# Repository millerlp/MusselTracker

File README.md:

This repository contains hardware designs and software to create a low-cost datalogger that can be used to track mussel (bivalve molluscs, not muscles) behavior  and temperature over long periods of time. The basic design includes a thermocouple temperature sensor, a hall effect magnetic sensor to sense valve gape, and a 3-D acclerometer/magnetometer to record mussel shell orientation.

Arduino-style code to run the datalogger is available the MusselTracker2 directory. The code requires the use of the MusselTrackerlib library available separately at https://github.com/millerlp/MusselTrackerlib 

Various testing code for individual sensors and the overall circuit board are available in the test_sketches directory. 

Circuit board designs are available in the Eagle_files directory.

Orginally a fork of https://github.com/andrewpetersen/MusselTracker/, now with a wholesale rewrite of the software and hardware. 

******************
    Copyright Luke Miller 2015

    This program is free software: you can redistribute it and/or modify
    it under the terms of the GNU General Public License as published by
    the Free Software Foundation, either version 3 of the License, or
    (at your option) any later version.

    This program is distributed in the hope that it will be useful,
    but WITHOUT ANY WARRANTY; without even the implied warranty of
    MERCHANTABILITY or FITNESS FOR A PARTICULAR PURPOSE.  See the
    GNU General Public License for more details.

    You should have received a copy of the GNU General Public License
    along with this program.  If not, see <http://www.gnu.org/licenses/>.

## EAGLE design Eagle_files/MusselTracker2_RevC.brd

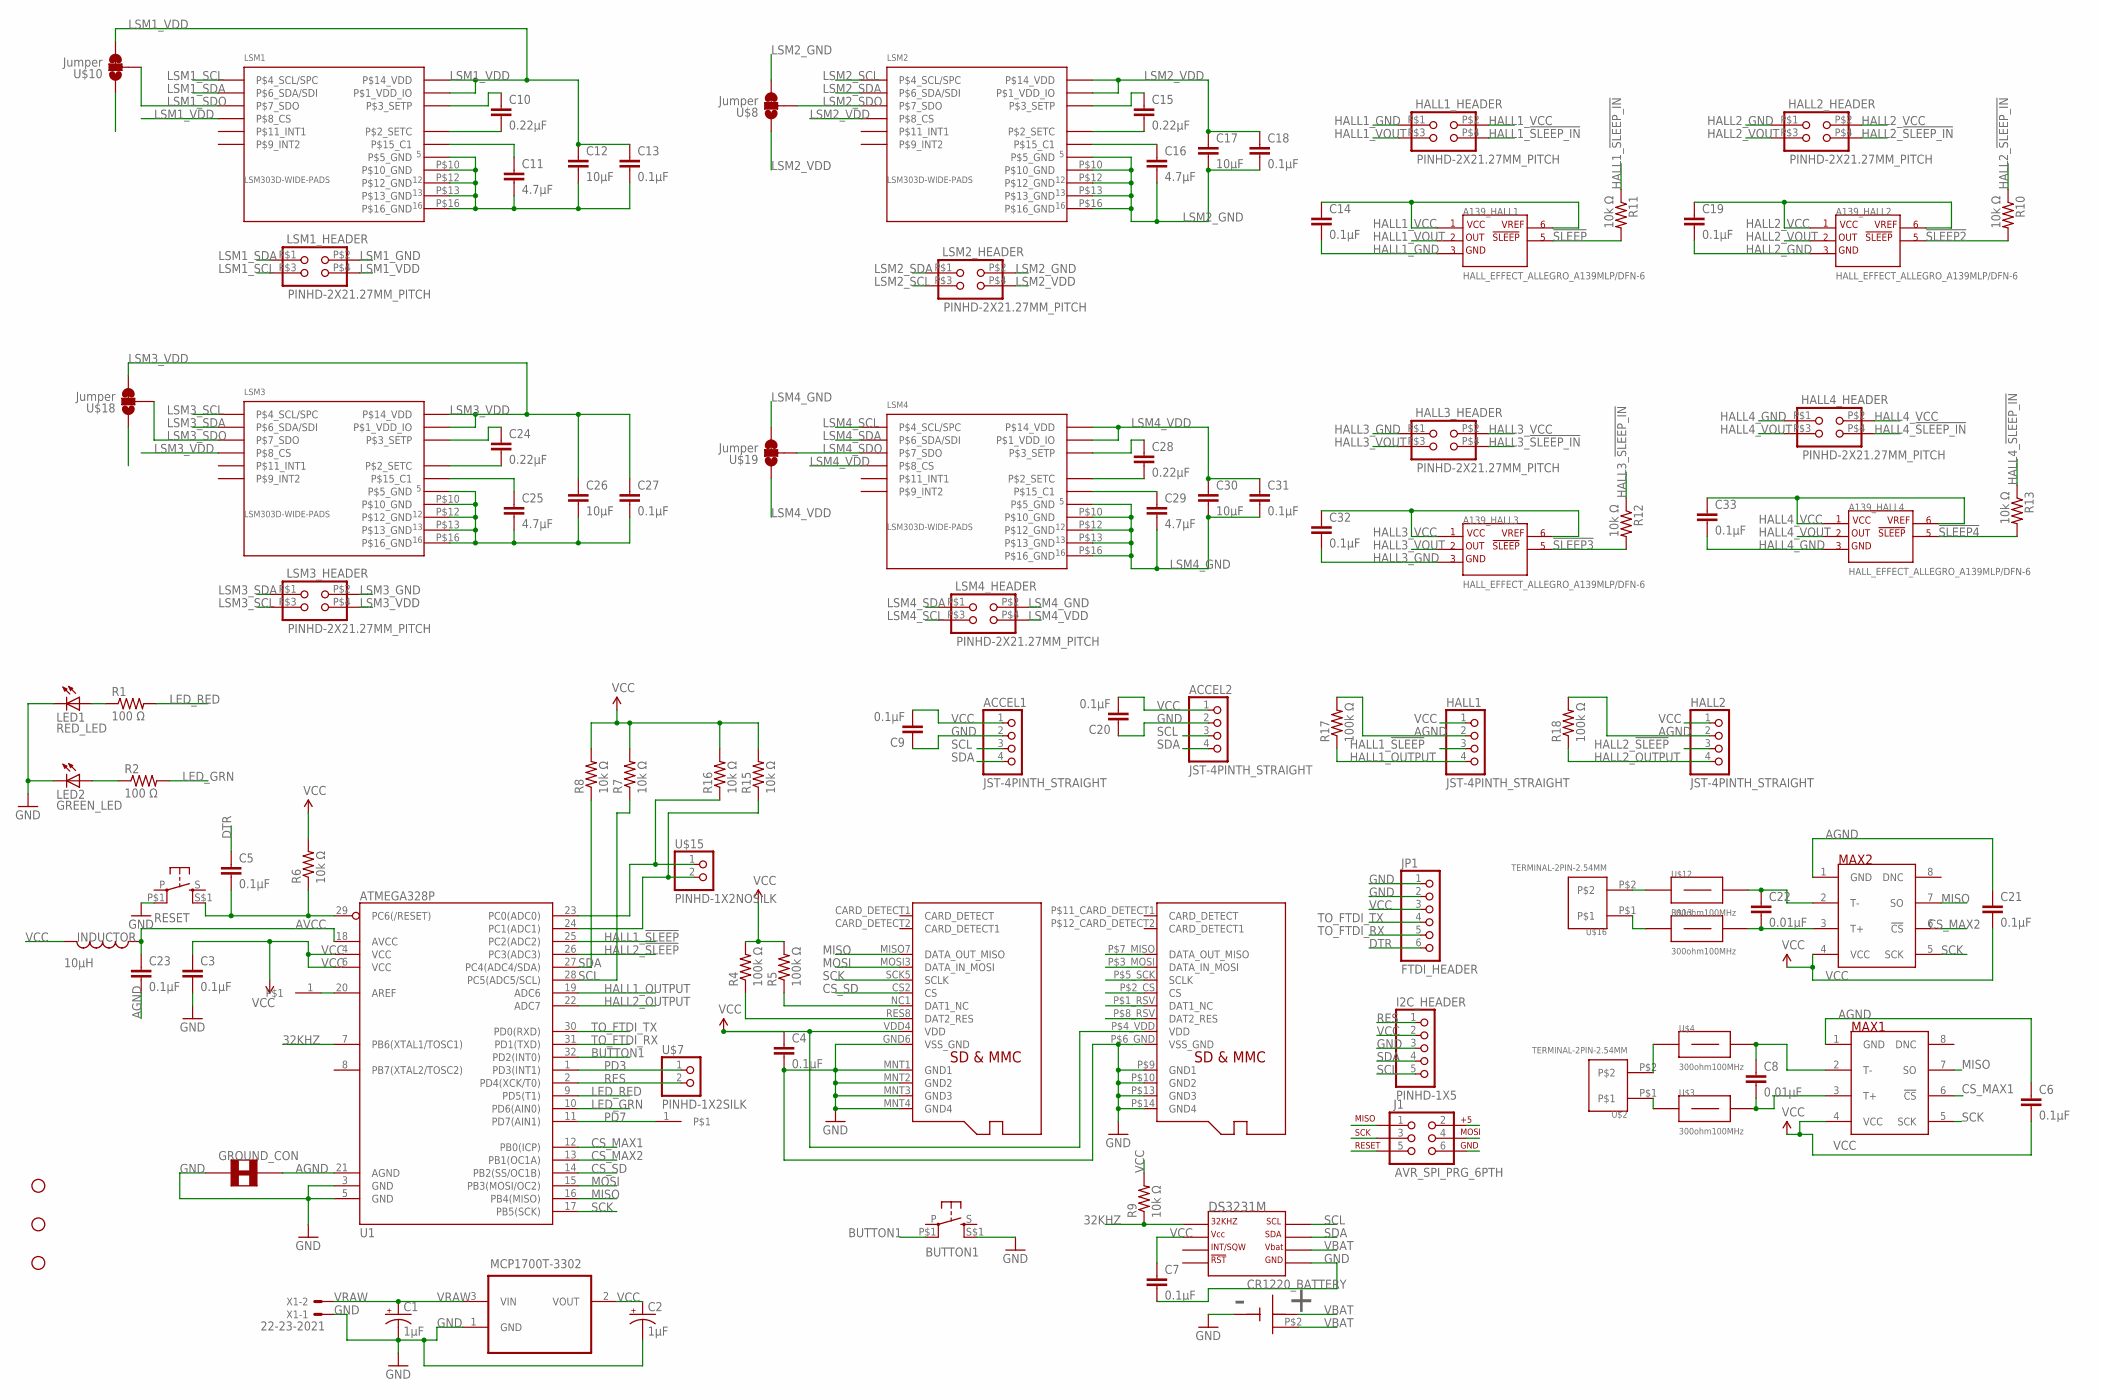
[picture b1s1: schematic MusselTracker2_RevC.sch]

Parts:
A139_HALL1, A139_HALL2, A139_HALL3, A139_HALL4: HALL_EFFECT_ALLEGRO_A139MLP/DFN-6; A139*_HALL_EFFECT
ACCEL1, ACCEL2: JST-4PINTH_STRAIGHT; JST-PH-4-THM
BUTTON1: PUSHBUTTON_DPST_SMD
C1, C2: 1µF; PANASONIC_B
C3, C4, C5, C6, C7, C9, C13, C14, C18, C19, C20, C21, C23, C27, C31, C32, C33: 0.1µF; 0805
C8, C22: 0.01µF; 0805_CAP_50V_KEMET
C10, C15, C24, C28: 0.22µF; 0805
C11, C16, C25, C29: 4.7µF; 0805
C12, C17, C26, C30: 10µF; 0805
CR1220_BATTERY: CR1220_BATTERY_HOLDERSMD; CR1220_BATTERY_HOLDER_SMD
DS3231M: DS3231MSOIC-8; DS3231M_SOIC8
GROUND_CON: SOLDER_JUMPER_TRACESTANDARD; SJ_2S-TRACE
HALL1, HALL2: JST-4PINTH_STRAIGHT; JST-PH-4-THM
HALL1_HEADER, HALL2_HEADER, HALL3_HEADER, HALL4_HEADER: PINHD-2X21.27MM_PITCH; 2X2_1.27MM
I2C_HEADER: PINHD-1X5; 1X05_BIGLOCK
INDUCTOR: 10µH; I_0805
J1: AVR_SPI_PRG_6PTH; 2X3
JP1: FTDI_HEADER; 1X06-BIGLOCK
LED1: RED_LED; CHIPLED_0805
LED2: GREEN_LED; CHIPLED_0805
LSM1, LSM2, LSM3, LSM4: LSM303D-WIDE-PADS; LSM303D
LSM1_HEADER, LSM2_HEADER, LSM3_HEADER, LSM4_HEADER: PINHD-2X21.27MM_PITCH; 2X2_1.27MM
MAX1, MAX2: MAX31855; SO08
MCP1700T-3302: MCP1700T-3302E/TT; SOT95P237X112-3N
R1, R2: 100 Ω; R0805
R4, R5, R17, R18: 100k Ω; R0805
R6, R7, R8, R9, R10, R11, R12, R13, R15, R16: 10k Ω; R0805
RESET: PUSHBUTTON_DPST_SMD
STANDOFF1, STANDOFF2, STANDOFF3: STAND-OFF
U1: ATMEGA328P; TQFP32-08
U$1: MICROSD_MOLEX_REVERSECURRENT; MICROSD_SOCKET_MOLEX_REVERSEMOUNT
U$2, U$16: TERMINAL-2PIN-2.54MM
U$3, U$4, U$12, U$13: 300ohm100MHz; 0805
U$6, U$17: PINHD-1X1SMALL; 1X01_SMALL
U$7: PINHD-1X2SILK; 1X02
U$8, U$10, U$18, U$19: Jumper; PAD-JUMPER-3-2OF3_NC_BY_TRACE_SMALL
U$14: MICROSD_MOLEX_REVERSEOBSOLETE; MICROSD_SOCKET_MOLEX_REVERSEMOUNT_OBSOLETE
U$15: PINHD-1X2NOSILK; 1X02_NOSILK
X1: 22-23-2021

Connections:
32KHZ: DS3231M.1 (P$1_32KHZ), R9.1, U1.7 (PB6(XTAL1/TOSC1))
!SLEEP: A139_HALL1.P$5, R11.2
!SLEEP2: A139_HALL2.P$5, R10.2
!SLEEP3: A139_HALL3.P$5, R12.2
!SLEEP4: A139_HALL4.P$5, R13.2
AGND: C6.1, C21.1, C23.2, GROUND_CON.2, HALL1.2, HALL2.2, MAX1.1 (GND), MAX2.1 (GND), R17.2, R18.2, U1.21 (AGND)
AVCC: C23.1, INDUCTOR.P$1 (1), U1.18 (AVCC)
BUTTON1: BUTTON1.P$1 (P1), U1.32 (PD2(INT0))
CS_MAX1: MAX1.6 (!CS), U1.12 (PB0(ICP))
CS_MAX2: MAX2.6 (!CS), U1.13 (PB1(OC1A))
CS_SD: U1.14 (PB2(SS/OC1B)), U$1.CS2 (CS), U$14.P$2_CS (CS)
DTR: C5.1, JP1.6
GND: ACCEL1.2, ACCEL2.2, BUTTON1.S$1 (S1), C1.-, C2.-, C3.2, C4.2, C7.2, C9.1, C20.1, CR1220_BATTERY.GND, DS3231M.5 (P$5_GND), GROUND_CON.1, I2C_HEADER.3, J1.6, JP1.1, JP1.2, LED1.C, LED2.C, MCP1700T-3302.1 (GND), RESET.P$1 (P1), U1.3 (GND), U1.5 (GND), U$1.GND6 (VSS_GND), U$1.MNT1 (GND1), U$1.MNT2 (GND2), U$1.MNT3 (GND3), U$1.MNT4 (GND4), U$14.P$6_GND (VSS_GND), U$14.P$9 (GND1), U$14.P$10 (GND2), U$14.P$13 (GND3), U$14.P$14 (GND4), X1.1
HALL1_!SLEEP: HALL1.3, U1.25 (PC2(ADC2))
HALL1_!SLEEP_IN: HALL1_HEADER.P$4 (4), R11.1
HALL1_GND: A139_HALL1.P$3_4, C14.2, HALL1_HEADER.P$1 (1)
HALL1_OUTPUT: HALL1.4, R17.1, U1.19 (ADC6)
HALL1_VCC: A139_HALL1.P$1, A139_HALL1.P$6, C14.1, HALL1_HEADER.P$2 (2)
HALL1_VOUT: A139_HALL1.P$2, HALL1_HEADER.P$3 (3)
HALL2_!SLEEP: HALL2.3, U1.26 (PC3(ADC3))
HALL2_!SLEEP_IN: HALL2_HEADER.P$4 (4), R10.1
HALL2_GND: A139_HALL2.P$3_4, C19.2, HALL2_HEADER.P$1 (1)
HALL2_OUTPUT: HALL2.4, R18.1, U1.22 (ADC7)
HALL2_VCC: A139_HALL2.P$1, A139_HALL2.P$6, C19.1, HALL2_HEADER.P$2 (2)
HALL2_VOUT: A139_HALL2.P$2, HALL2_HEADER.P$3 (3)
HALL3_!SLEEP_IN: HALL3_HEADER.P$4 (4), R12.1
HALL3_GND: A139_HALL3.P$3_4, C32.2, HALL3_HEADER.P$1 (1)
HALL3_VCC: A139_HALL3.P$1, A139_HALL3.P$6, C32.1, HALL3_HEADER.P$2 (2)
HALL3_VOUT: A139_HALL3.P$2, HALL3_HEADER.P$3 (3)
HALL4_!SLEEP_IN: HALL4_HEADER.P$4 (4), R13.1
HALL4_GND: A139_HALL4.P$3_4, C33.2, HALL4_HEADER.P$1 (1)
HALL4_VCC: A139_HALL4.P$1, A139_HALL4.P$6, C33.1, HALL4_HEADER.P$2 (2)
HALL4_VOUT: A139_HALL4.P$2, HALL4_HEADER.P$3 (3)
LED_GRN: R2.2, U1.10 (PD6(AIN0))
LED_RED: R1.2, U1.9 (PD5(T1))
LSM1_GND: C11.2, C12.2, C13.2, LSM1.P$5 (P$5_GND), LSM1.P$10 (P$10_GND), LSM1.P$12 (P$12_GND), LSM1.P$13 (P$13_GND), LSM1.P$16 (P$16_GND), LSM1_HEADER.P$2 (2), U$10.1
LSM1_SCL: LSM1.P$4 (P$4_SCL/SPC), LSM1_HEADER.P$3 (3)
LSM1_SDA: LSM1.P$6 (P$6_SDA/SDI), LSM1_HEADER.P$1 (1)
LSM1_SDO: LSM1.P$7 (P$7_SDO), U$10.2
LSM1_VDD: C12.1, C13.1, LSM1.P$1 (P$1_VDD_IO), LSM1.P$8 (P$8_CS), LSM1.P$14 (P$14_VDD), LSM1_HEADER.P$4 (4), U$10.3
LSM2_GND: C16.2, C17.2, C18.2, LSM2.P$5 (P$5_GND), LSM2.P$10 (P$10_GND), LSM2.P$12 (P$12_GND), LSM2.P$13 (P$13_GND), LSM2.P$16 (P$16_GND), LSM2_HEADER.P$2 (2), U$8.3
LSM2_SCL: LSM2.P$4 (P$4_SCL/SPC), LSM2_HEADER.P$3 (3)
LSM2_SDA: LSM2.P$6 (P$6_SDA/SDI), LSM2_HEADER.P$1 (1)
LSM2_SDO: LSM2.P$7 (P$7_SDO), U$8.2
LSM2_VDD: C17.1, C18.1, LSM2.P$1 (P$1_VDD_IO), LSM2.P$8 (P$8_CS), LSM2.P$14 (P$14_VDD), LSM2_HEADER.P$4 (4), U$8.1
LSM3_GND: C25.2, C26.2, C27.2, LSM3.P$5 (P$5_GND), LSM3.P$10 (P$10_GND), LSM3.P$12 (P$12_GND), LSM3.P$13 (P$13_GND), LSM3.P$16 (P$16_GND), LSM3_HEADER.P$2 (2), U$18.1
LSM3_SCL: LSM3.P$4 (P$4_SCL/SPC), LSM3_HEADER.P$3 (3)
LSM3_SDA: LSM3.P$6 (P$6_SDA/SDI), LSM3_HEADER.P$1 (1)
LSM3_SDO: LSM3.P$7 (P$7_SDO), U$18.2
LSM3_VDD: C26.1, C27.1, LSM3.P$1 (P$1_VDD_IO), LSM3.P$8 (P$8_CS), LSM3.P$14 (P$14_VDD), LSM3_HEADER.P$4 (4), U$18.3
LSM4_GND: C29.2, C30.2, C31.2, LSM4.P$5 (P$5_GND), LSM4.P$10 (P$10_GND), LSM4.P$12 (P$12_GND), LSM4.P$13 (P$13_GND), LSM4.P$16 (P$16_GND), LSM4_HEADER.P$2 (2), U$19.3
LSM4_SCL: LSM4.P$4 (P$4_SCL/SPC), LSM4_HEADER.P$3 (3)
LSM4_SDA: LSM4.P$6 (P$6_SDA/SDI), LSM4_HEADER.P$1 (1)
LSM4_SDO: LSM4.P$7 (P$7_SDO), U$19.2
LSM4_VDD: C30.1, C31.1, LSM4.P$1 (P$1_VDD_IO), LSM4.P$8 (P$8_CS), LSM4.P$14 (P$14_VDD), LSM4_HEADER.P$4 (4), U$19.1
MISO: J1.1, MAX1.7 (SO), MAX2.7 (SO), U1.16 (PB4(MISO)), U$1.MISO7 (DATA_OUT_MISO), U$14.P$7_MISO (DATA_OUT_MISO)
MOSI: J1.4, U1.15 (PB3(MOSI/OC2)), U$1.MOSI3 (DATA_IN_MOSI), U$14.P$3_MOSI (DATA_IN_MOSI)
unnamed: U$2.P$2, U$4.1
unnamed: LED1.A, R1.1
unnamed: U$2.P$1, U$3.1
unnamed: C11.1, LSM1.P$15 (P$15_C1)
unnamed: C10.2, LSM1.P$2 (P$2_SETC)
unnamed: R16.1, U1.23 (PC0(ADC0)), U$15.1
unnamed: U1.20 (AREF), U$17.1
unnamed: R15.1, U1.24 (PC1(ADC1)), U$15.2
unnamed: LED2.A, R2.1
unnamed: U$12.1, U$16.P$2
unnamed: U$13.1, U$16.P$1
unnamed: C24.2, LSM3.P$2 (P$2_SETC)
unnamed: C24.1, LSM3.P$3 (P$3_SETP)
unnamed: C10.1, LSM1.P$3 (P$3_SETP)
unnamed: C15.2, LSM2.P$2 (P$2_SETC)
unnamed: C15.1, LSM2.P$3 (P$3_SETP)
unnamed: C16.1, LSM2.P$15 (P$15_C1)
unnamed: C25.1, LSM3.P$15 (P$15_C1)
unnamed: C28.1, LSM4.P$3 (P$3_SETP)
unnamed: C28.2, LSM4.P$2 (P$2_SETC)
unnamed: C29.1, LSM4.P$15 (P$15_C1)
NC1: R5.1, U$1.NC1 (DAT1_NC), U$14.P$1_RSV (DAT1_NC)
PD3: U1.1 (PD3(INT1)), U$7.1
PD7: U1.11 (PD7(AIN1)), U$6.1
RES: I2C_HEADER.1, U1.2 (PD4(XCK/T0)), U$7.2
RES8: R4.1, U$1.RES8 (DAT2_RES), U$14.P$8_RSV (DAT2_RES)
RESET: C5.2, J1.5, R6.1, RESET.S$1 (S1), U1.29 (PC6(/RESET))
SCK: J1.3, MAX1.5 (SCK), MAX2.5 (SCK), U1.17 (PB5(SCK)), U$1.SCK5 (SCLK), U$14.P$5_SCK (SCLK)
SCL: ACCEL1.3, ACCEL2.3, DS3231M.8 (P$8_SCL), I2C_HEADER.5, R7.1, U1.28 (PC5(ADC5/SCL))
SDA: ACCEL1.4, ACCEL2.4, DS3231M.7 (P$7_SDA), I2C_HEADER.4, R8.1, U1.27 (PC4(ADC4/SDA))
T+_MAX1: C8.2, MAX1.3 (T+), U$3.2
T+_MAX2: C22.2, MAX2.3 (T+), U$13.2
T-_MAX1: C8.1, MAX1.2 (T-), U$4.2
T-_MAX2: C22.1, MAX2.2 (T-), U$12.2
TO_FTDI_RX: JP1.5, U1.31 (PD1(TXD))
TO_FTDI_TX: JP1.4, U1.30 (PD0(RXD))
VBAT: CR1220_BATTERY.P$1 (VBAT), CR1220_BATTERY.P$2, DS3231M.6 (P$6_VBAT)
VCC: ACCEL1.1, ACCEL2.1, C2.+, C3.1, C4.1, C6.2, C7.1, C9.2, C20.2, C21.2, DS3231M.2 (P$2_VCC), HALL1.1, HALL2.1, I2C_HEADER.2, INDUCTOR.P$2 (2), J1.2, JP1.3, MAX1.4 (VCC), MAX2.4 (VCC), MCP1700T-3302.2 (VOUT), R4.2, R5.2, R6.2, R7.2, R8.2, R9.2, R15.2, R16.2, U1.4 (VCC), U1.6 (VCC), U$1.VDD4 (VDD), U$14.P$4_VDD (VDD)
VRAW: C1.+, MCP1700T-3302.3 (VIN), X1.2

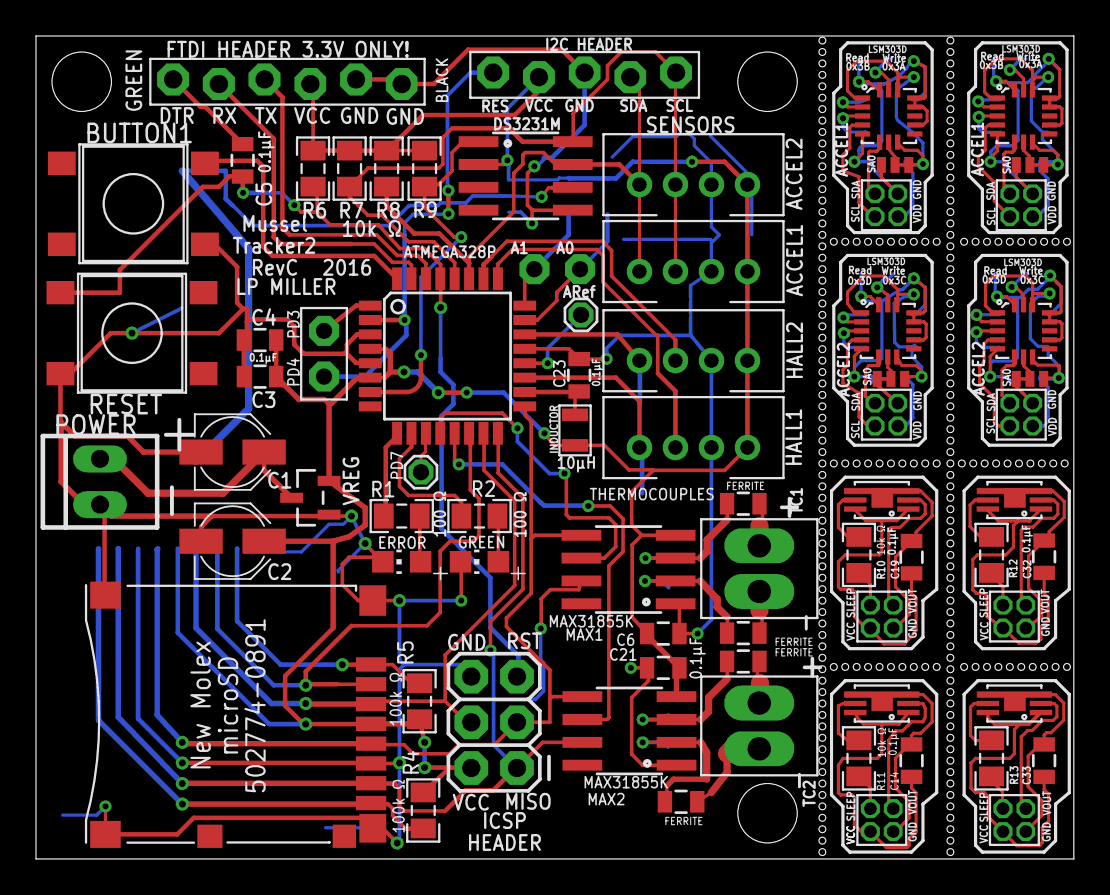
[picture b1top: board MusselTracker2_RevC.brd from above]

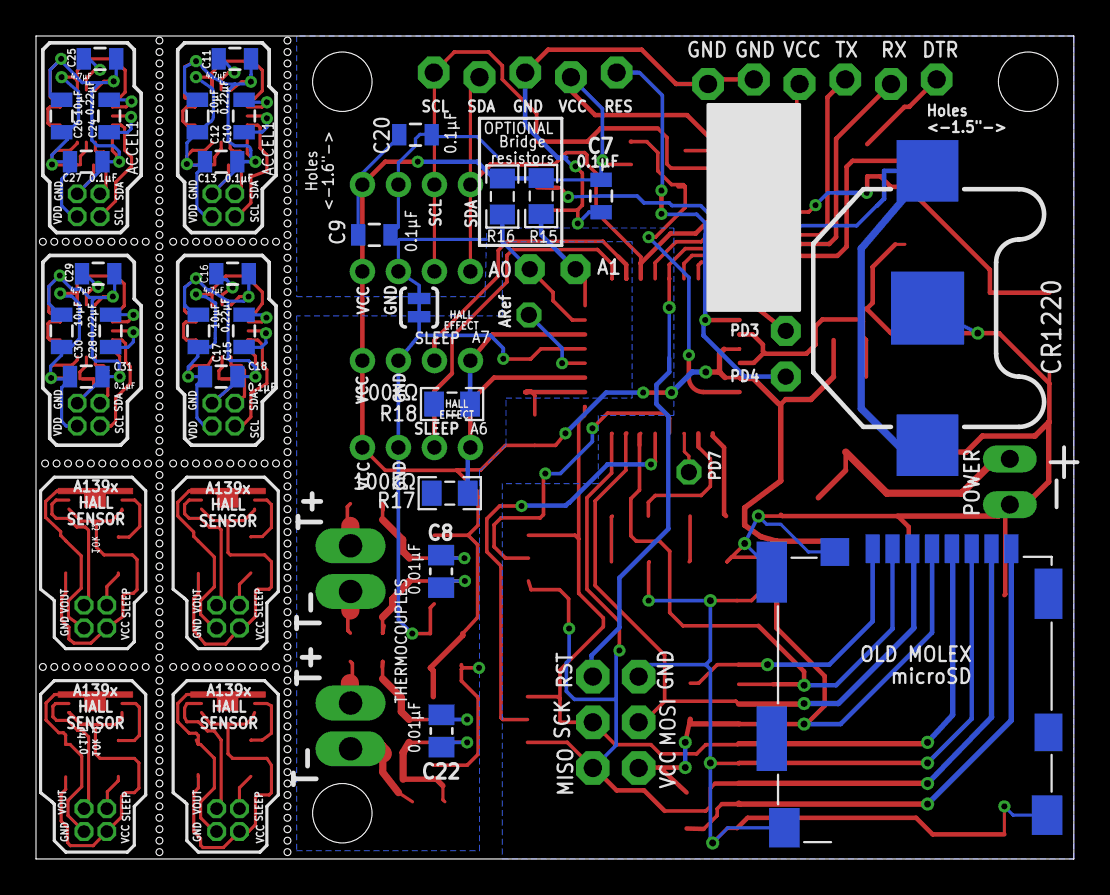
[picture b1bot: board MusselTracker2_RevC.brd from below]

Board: 2 copper layers, 57.7 x 45.7 mm, 104 parts (28 on the bottom side), 96 nets.

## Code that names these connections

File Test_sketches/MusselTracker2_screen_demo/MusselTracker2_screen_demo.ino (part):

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
#define ERRLED 5		// Red error LED pin
#define GREENLED 6		// Green LED pin
#define BUTTON1 2 		// BUTTON1 on INT0, pin PD2

// Comment out the following line to remove parts of the
// test code from functioning. 
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
//************
// Define MAX31855 objects, need 2 of them for the two separate chips
#define CS_MAX1 8 // Chip Select for MAX31855 #1
#define CS_MAX2 9 // Chip Select for MAX31855 #2
Adafruit_MAX31855 thermocouple1(CS_MAX1);
Adafruit_MAX31855 thermocouple2(CS_MAX2);
double temp1 = 0; // hold output from MAX31855 #1
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volatile unsigned long buttonTime1; // hold the initial button press millis() value
byte debounceTime = 20; // milliseconds to wait for debounce
volatile bool buttonFlag = false; // Flag to mark when button was pressed
byte mediumPressTime = 2; // seconds to hold button1 to register a medium press
byte longPressTime = 5; // seconds to hold button1 to register a long press
byte pressCount = 0; // counter for number of button presses
unsigned long prevMillis;	// counter for faster operations
unsigned long newMillis;	// counter for faster operations
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//---------------- setup loop ------------------------------------------------
void setup() {
	// Set button1 as an input
	pinMode(BUTTON1, INPUT_PULLUP);
	// Register an interrupt on INT0, attached to button1
	// which will call buttonFunc when the button is pressed.
	attachInterrupt(0, buttonFunc, LOW);
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	digitalWrite(GREENLED, LOW);
	// Set the SPI bus chip select pins as outputs
	// for the two MAX31855 thermocouple chips
	pinMode(CS_MAX1, OUTPUT);
	digitalWrite(CS_MAX1, HIGH);
	pinMode(CS_MAX2, OUTPUT);
	digitalWrite(CS_MAX2, HIGH);

	pinMode(4, OUTPUT);
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
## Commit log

2015-05-05 Initial fork of github.com/andrewpetersen/MusselTracker/
2015-05-06 Just a simple blink sketch to show that the bootloader works and allows serial uploading.
2015-05-06 Entry for a boards.txt file so that Arduino IDE knows how to handle the MusselTracker v1 boards.
2015-05-06 Nothing new here currently, just making a copy of the original sketch from version 1.
2015-05-10 Just changing the blink
2015-06-11 Trying to test out assembled boards with these sketches
2015-06-13 This probably doesn't work with the newest version of the mussel tracker library, but it did work at one point
2015-06-13 Just a quick test of a prototype library for the
    Allegro hall effect sensors. It worked originally, but I think the library
    has changed enough that it won't work in the future.
2015-06-13 Tested as working with MusselTracker v2 RevB breakout board
2015-06-16 Added a test bench system for the LSM breakout.s
2015-06-29 First commit, nothing to see yet
2015-06-29 Rearranged the output to serial
2015-06-29 Updated to burn the last of the boards. This shouldn't be needed any further.
2015-06-29 Updated to put in new time value
2015-06-29 Updated references to new library name
2015-06-29 Minimal functional version, with file naming, serial number extraction, temperature recording to SD at 1 second intervals.
2015-06-30 Dealing with serial number output, added error code explanations.
2015-06-30 Had to re-burn some serial numbers for some reason
2015-06-30 Had to reset a few rtcs
2015-07-02 Reformatting the output and changing uppercase RTC to lowercase
2015-07-02 Beginning the actual data collection program in earnest. Need to add calibration routine and handling button presses.
2015-07-02 Added the basic bones of a button interrupt and enter calibration mode section of code.
2015-07-02 This was working up until 5 minutes ago
2015-07-02 Fixed bug trying to send DateTime object directly to Serial.print() that was causing a compile hang with no errors.
2015-07-06 Make the flag voltatile
2015-07-06 Fleshed out the remainder of the calibration states. Need to check into changing accel sample rate during calibration mode.
2015-07-06 Added code to switch accel into high-frequency sampling mode during calibration. Finished up the calibration routine, including adding directions at the top of the program. Added some pin toggles to 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
2015-07-07 Needed to put the serial print delay back to 10ms so it would read out properly.
2015-07-07 Added flags for various failures of sensors, but need to come up with a time-efficient way to signal failures via the LEDs.
2015-07-07 Got rid of this empty file
2015-07-07 Added flashing for error codes when sensors fail, added comments for preamble to make sense of the error flashes.
2015-07-07 Updated to current working version
2015-07-07 Added code to make use of MCU status register to look for brownout events and force the avr into a low-power sleep mode if a brownout occurs. Also modified the output file header to include the MCUSR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
2015-07-07 Updating with new times
2015-07-07 Adding error code for brownout situation, set green led pulse interval to 10. Loaded this version up to all 15 boards on 2015-07-07 16:00
2015-07-08 Reverted to accel defaults for normal data taking mode. The anti-aliasing filter was probably not enabled correctly by me.
2015-07-08 Updated with new time
2015-07-08 Fleshed out the various filter settings for the accelerometer, settled on settings for calibration and normal data modes. We don't want the high-pass filter enabled on the accel channel since that el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
2015-07-08 Swapped out time-reset utility program for an easier version that works from the serial monitor.
2015-07-10 Added function getaccelSettings to read accelerometer/magnetometer settings and then write them to the headers of the output files.
2015-07-11 Attempt at stopping the bogus data writes
2015-07-11 Adding code to overwrite bad hall readings with -9999
2015-07-11 Changed if(loopCount) test to == instead of >= to see if that quells any bogus SD writes.
2015-07-12 Changing the magnetometer range to +/- 8 gauss to minimize the chances of neighboring magnets possibly railing the sensor. Altered the calibration anti-alias filter to 50Hz for the accelerometer sinc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
2015-07-13 Added green LED blink every 10 seconds to help see how well adjacent MusselTracker boards are synchronized.
2016-06-28 Added code to check if accel or magnetometer values are repeating constantly, which signals a non-functional sensor and should light the red error LED.
2016-06-29 Simple program to output accel/mag raw data to Serial
    Run this with the Serial Monitor open to see a live stream of
    accelerometer and magnetometer. This will only work with a single
    LSM303D chip attached, and it must be the version with the sa0 pin
    pulled high.
2016-06-30 Adding comment for red light error code
2016-07-14 Adding board schematics
2016-07-19 Updating for board builds
2016-07-19 Updating for new board builds
2016-07-26 new serial
2016-12-06 Speeding up test sketch data rate
2017-03-05 Adding explanation of subdirectories.
2017-05-27 Link to MusselTrackerlib
2017-05-27 Clarify the purpose a bit.
2017-05-27 Adding GPL v3 license verbiage
2017-05-27 Adding license file, GPL v3
2017-05-27 Including license verbiage
2017-05-27 Formatting
2018-01-03 Demo sketch for OLED screen
    This version hooks to a I2C OLED 128x64 display screen to show updates of the two temperature channels and one Hall effect channel for classroom demonstration.
2019-08-21 Eagle design files

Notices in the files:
Test_sketches/MusselTracker2_screen_demo/MusselTracker2_screen_demo.ino:
Copyright Luke Miller 2018
